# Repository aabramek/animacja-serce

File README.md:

# animacja-serce
Płytka z ledami ułożonymi w kształ serca
do wyświetlania animacji

## Obsługa
Ustawienie parametrów jest realizowane przez ustawienia

+ Wyboru animacji

+ Czasu między kolejnymi krokami animacji

+ Jasności diod

Krótkie przyciśnięcie przycisku zmienia wartość wybranego ustawienia np. kolejna animacja lub zwiększenie jasności
Kierunek zmian jest w jedną stronę, aby przejść na początek trzeba przejść przez wszystkie wartości

Długie przyciśnięcie przycisku przełącza się między ustawieniami

## To do:

Zmiana formatu animacji z wbudowanych w program funkcji na kod możliwy do zapisania w pamięci np. EEPROM i późniejszego 
załadowania i zinterpretowania przez program

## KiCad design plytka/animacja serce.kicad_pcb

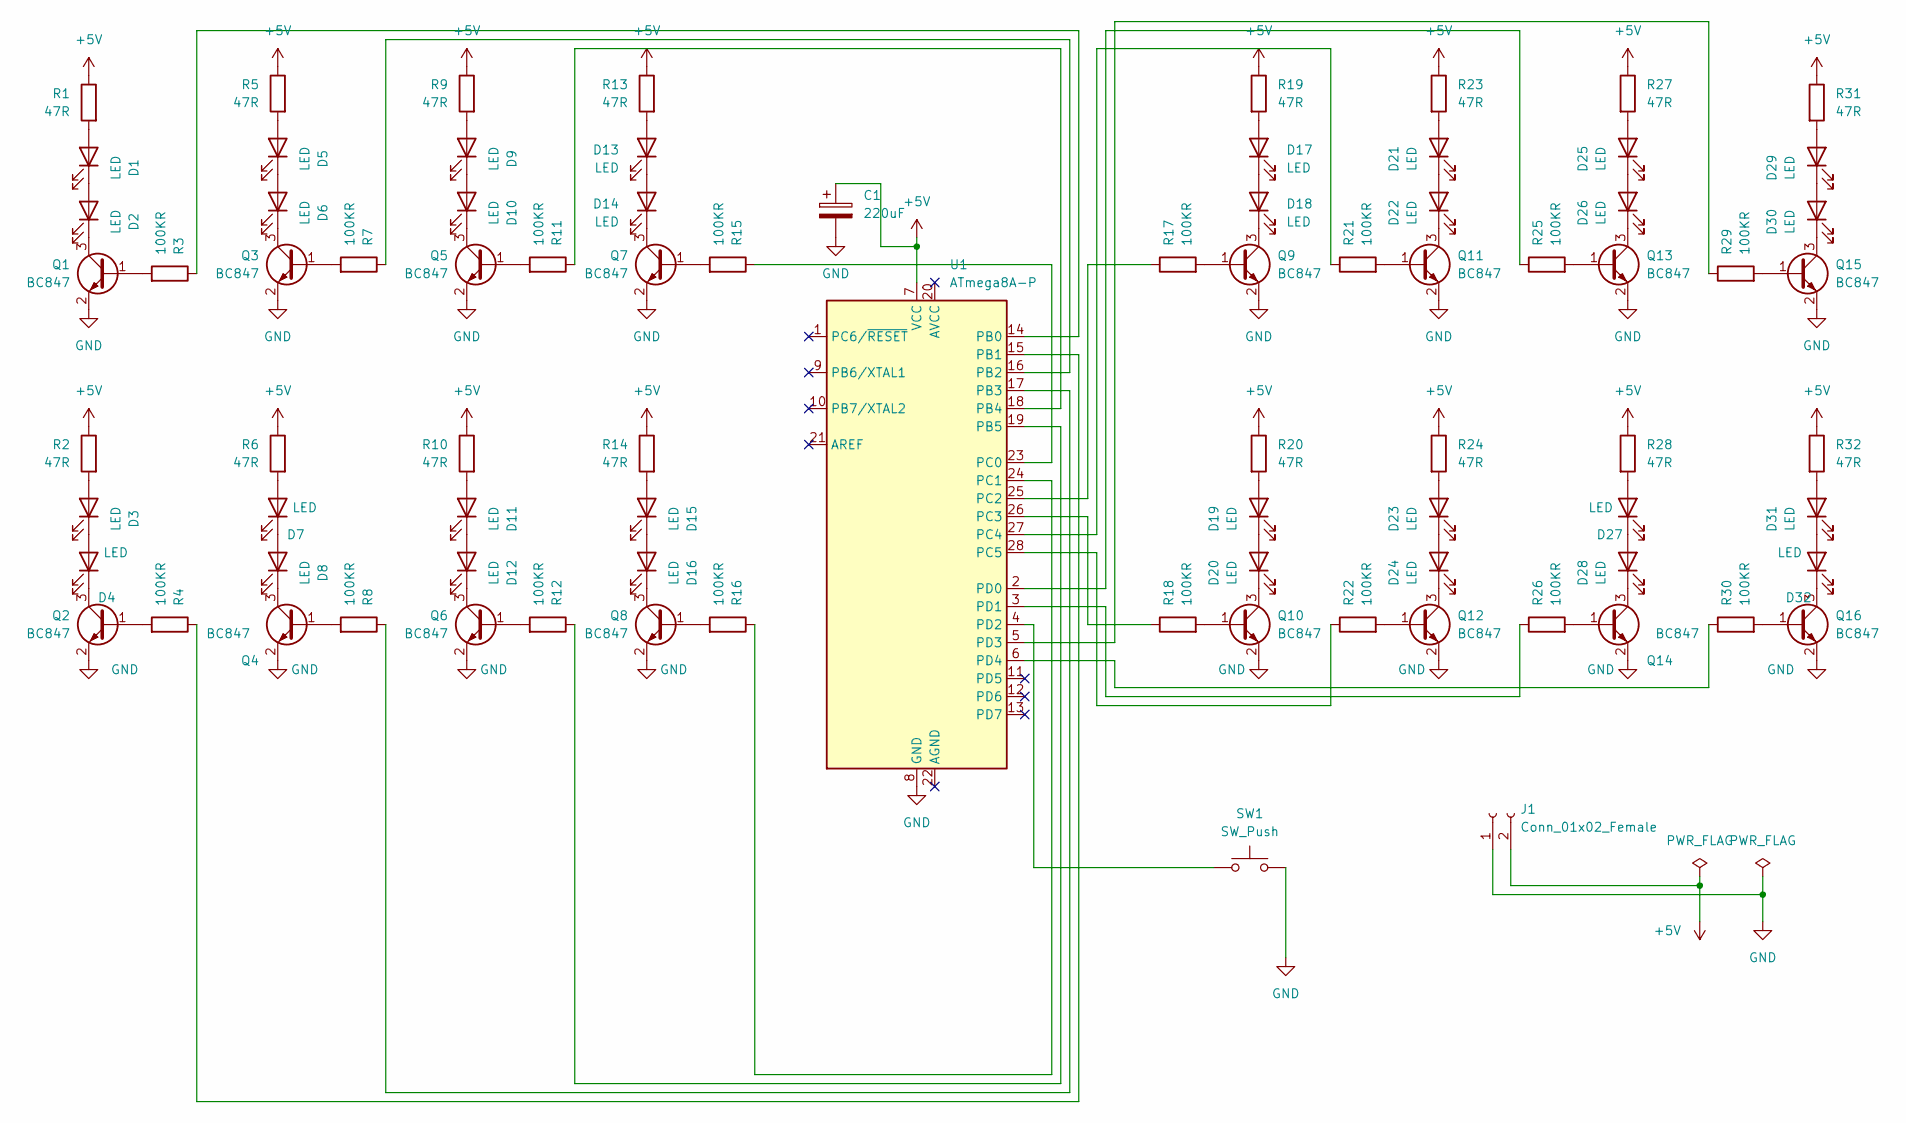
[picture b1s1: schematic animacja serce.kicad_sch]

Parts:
C1: 220uF; CP_Radial_D6.3mm_P2.50mm
D1, D2, D3, D4, D5, D6, D7, D8, D9, D10, D11, D12, D13, D14, D15, D16, D17, D18, D19, D20, D21, D22, D23, D24, D25, D26, D27, D28, D29, D30, D31, D32: LED; LED_1210_3225Metric_Pad1.42x2.65mm_HandSolder
J1: Conn_01x02_Female; SolderWire-2.5sqmm_1x02_P7.2mm_D2.4mm_OD3.6mm
Q1, Q2, Q3, Q4, Q5, Q6, Q7, Q8, Q9, Q10, Q11, Q12, Q13, Q14, Q15, Q16: BC847; SOT-23
R1, R2, R5, R6, R9, R10, R13, R14, R19, R20, R23, R24, R27, R28, R31, R32: 47R; R_1206_3216Metric_Pad1.30x1.75mm_HandSolder
R3, R4, R7, R8, R11, R12, R15, R16, R17, R18, R21, R22, R25, R26, R29, R30: 100KR; R_1206_3216Metric_Pad1.30x1.75mm_HandSolder
SW1: SW_Push; R_Axial_DIN0207_L6.3mm_D2.5mm_P5.08mm_Vertical
U1: ATmega8A-P; DIP-28_W7.62mm

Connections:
+5V: C1.1, J1.2, R1.1, R2.1, R5.1, R6.1, R9.1, R10.1, R13.1, R14.1, R19.1, R20.1, R23.1, R24.1, R27.1, R28.1, R31.1, R32.1, U1.7 (VCC)
GND: C1.2, J1.1, Q1.2 (E), Q2.2 (E), Q3.2 (E), Q4.2 (E), Q5.2 (E), Q6.2 (E), Q7.2 (E), Q8.2 (E), Q9.2 (E), Q10.2 (E), Q11.2 (E), Q12.2 (E), Q13.2 (E), Q14.2 (E), Q15.2 (E), Q16.2 (E), SW1.2, U1.8 (GND)
unnamed: D1.1 (K), D2.2 (A)
unnamed: D1.2 (A), R1.2
unnamed: D2.1 (K), Q1.3 (C)
unnamed: D3.1 (K), D4.2 (A)
unnamed: D3.2 (A), R2.2
unnamed: D4.1 (K), Q2.3 (C)
unnamed: D5.1 (K), D6.2 (A)
unnamed: D5.2 (A), R5.2
unnamed: D6.1 (K), Q3.3 (C)
unnamed: D7.1 (K), D8.2 (A)
unnamed: D7.2 (A), R6.2
unnamed: D8.1 (K), Q4.3 (C)
unnamed: D9.2 (A), R9.2
unnamed: D10.1 (K), Q5.3 (C)
unnamed: D9.1 (K), D10.2 (A)
unnamed: D11.1 (K), D12.2 (A)
unnamed: D11.2 (A), R10.2
unnamed: D12.1 (K), Q6.3 (C)
unnamed: D13.1 (K), D14.2 (A)
unnamed: D13.2 (A), R13.2
unnamed: D14.1 (K), Q7.3 (C)
unnamed: D15.1 (K), D16.2 (A)
unnamed: D15.2 (A), R14.2
unnamed: D16.1 (K), Q8.3 (C)
unnamed: D17.1 (K), D18.2 (A)
unnamed: D17.2 (A), R19.2
unnamed: D18.1 (K), Q9.3 (C)
unnamed: D19.1 (K), D20.2 (A)
unnamed: D19.2 (A), R20.2
unnamed: D20.1 (K), Q10.3 (C)
unnamed: D21.1 (K), D22.2 (A)
unnamed: D21.2 (A), R23.2
unnamed: D22.1 (K), Q11.3 (C)
unnamed: D23.1 (K), D24.2 (A)
unnamed: D23.2 (A), R24.2
unnamed: D24.1 (K), Q12.3 (C)
unnamed: D25.1 (K), D26.2 (A)
unnamed: D25.2 (A), R27.2
unnamed: D26.1 (K), Q13.3 (C)
unnamed: D27.1 (K), D28.2 (A)
unnamed: D27.2 (A), R28.2
unnamed: D28.1 (K), Q14.3 (C)
unnamed: D29.1 (K), D30.2 (A)
unnamed: D29.2 (A), R31.2
unnamed: D30.1 (K), Q15.3 (C)
unnamed: D31.1 (K), D32.2 (A)
unnamed: D31.2 (A), R32.2
unnamed: D32.1 (K), Q16.3 (C)
unnamed: Q1.1 (B), R3.2
unnamed: Q2.1 (B), R4.2
unnamed: Q3.1 (B), R7.2
unnamed: Q4.1 (B), R8.2
unnamed: Q5.1 (B), R11.2
unnamed: Q6.1 (B), R12.2
unnamed: Q7.1 (B), R15.2
unnamed: Q8.1 (B), R16.2
unnamed: Q9.1 (B), R17.2
unnamed: Q10.1 (B), R18.2
unnamed: Q11.1 (B), R21.2
unnamed: Q12.1 (B), R22.2
unnamed: Q13.1 (B), R25.2
unnamed: Q14.1 (B), R26.2
unnamed: Q15.1 (B), R29.2
unnamed: Q16.1 (B), R30.2
unnamed: R3.1, U1.14 (PB0)
unnamed: R4.1, U1.15 (PB1)
unnamed: R7.1, U1.16 (PB2)
unnamed: R8.1, U1.17 (PB3)
unnamed: R11.1, U1.18 (PB4)
unnamed: R12.1, U1.19 (PB5)
unnamed: R15.1, U1.23 (PC0)
unnamed: R16.1, U1.24 (PC1)
unnamed: R17.1, U1.25 (PC2)
unnamed: R18.1, U1.26 (PC3)
unnamed: R21.1, U1.27 (PC4)
unnamed: R22.1, U1.28 (PC5)
unnamed: R25.1, U1.2 (PD0)
unnamed: R26.1, U1.3 (PD1)
unnamed: R29.1, U1.5 (PD3)
unnamed: R30.1, U1.6 (PD4)
unnamed: SW1.1, U1.4 (PD2)

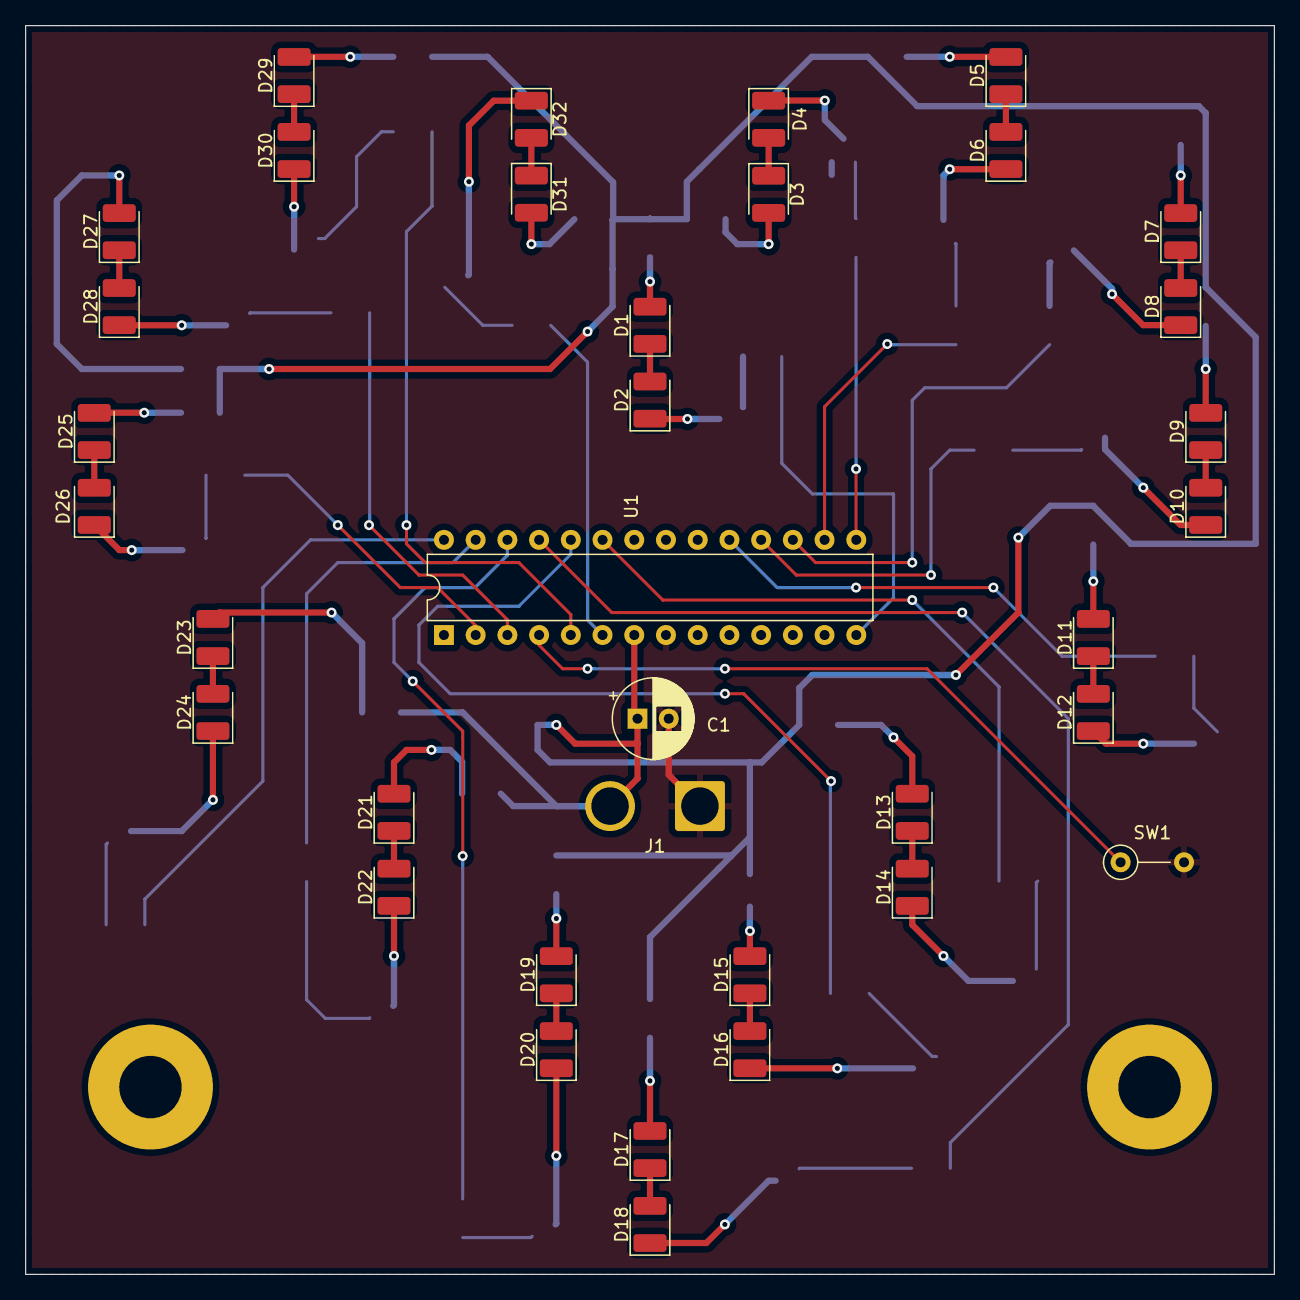
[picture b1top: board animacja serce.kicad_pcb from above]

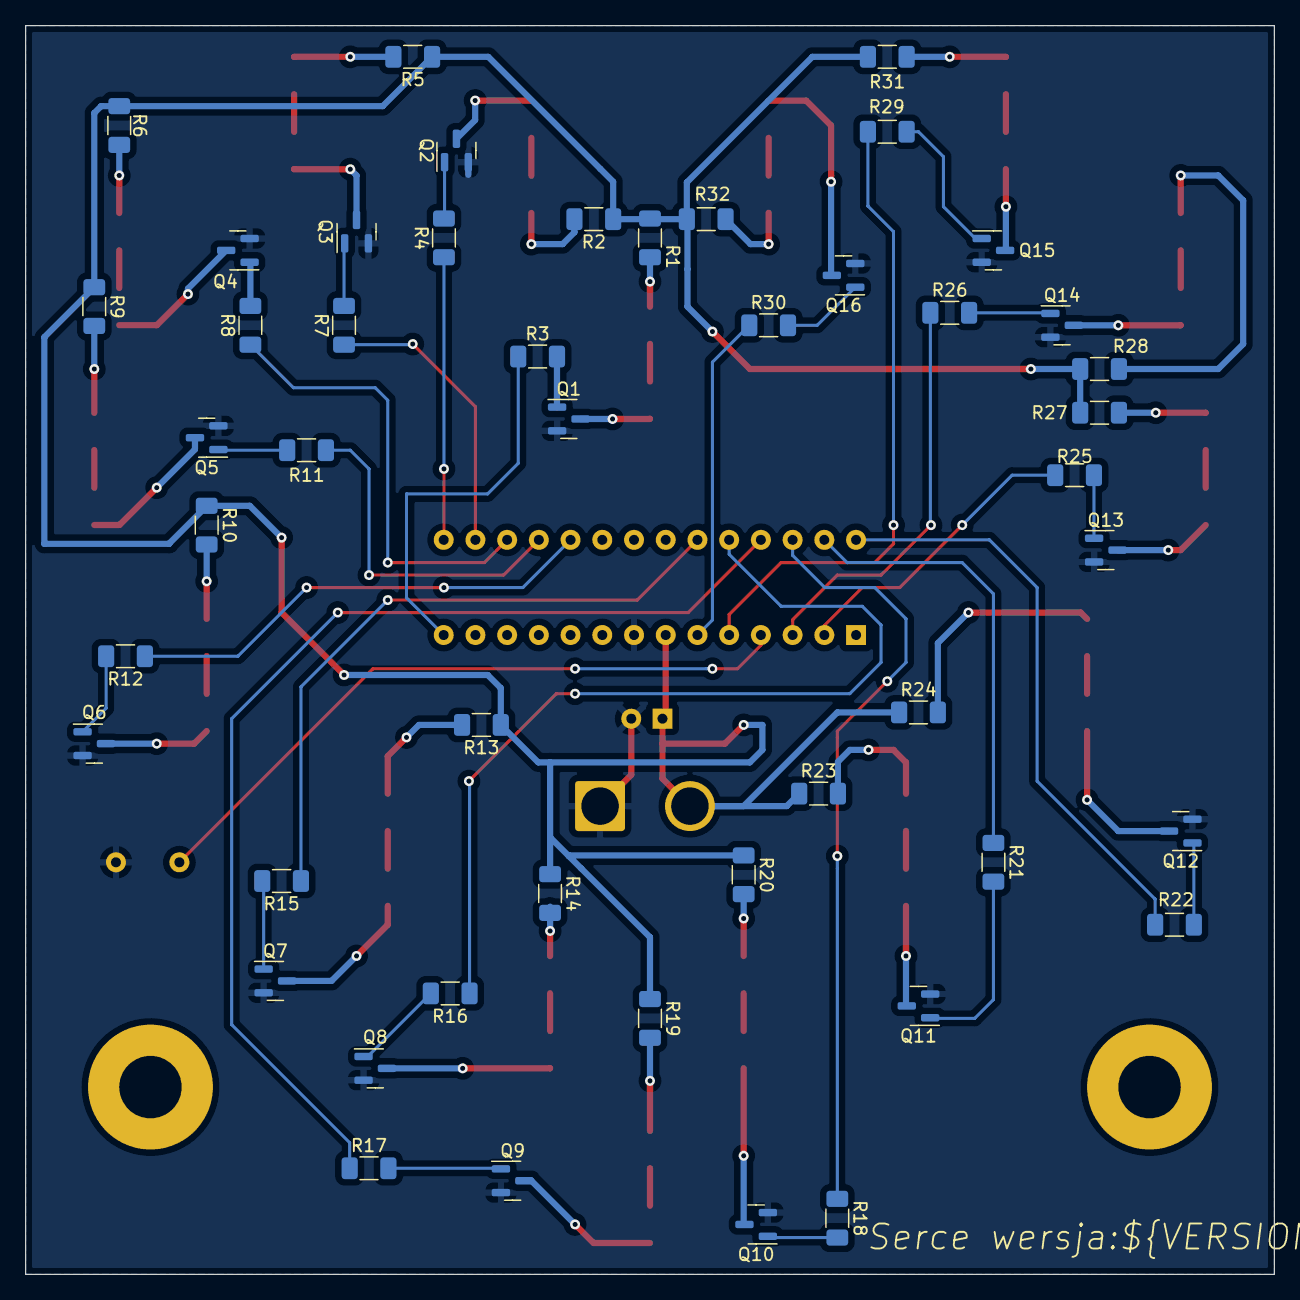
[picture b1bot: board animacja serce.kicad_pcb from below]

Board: 2 copper layers, 100.0 x 100.0 mm, 84 parts (48 on the bottom side), 83 nets.

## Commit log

2023-01-03 Pierwsza wersja
2023-01-03 Dodane README
